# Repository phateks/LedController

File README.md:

# LED Controller (ESP32-C3-Mini)

<table>
	<tr>
		<td></td>
		<td></td>
	</tr>
</table>

## Power
- Input: 12 or 24 VDC on J1 connector

## Connections for Digital LED
- DO (DATA) 
- LED+ = VCC
- LED- = GND

## Connections for Classic LED
- LED+ = VCC
- Dim- = GND

## External Switch (Momentary)

- S1 - Dim down
- S2 - Dim up
- Com - Second connection on the switch (common for both)

## GPIO Config

- IO4: DATA LED
- IO5: PWM LED
- IO6: Dim Up
- IO7: Dim Down
- TXD0/RXD0: 
- EN: reset/enable
- BOOT: bootloader (IO09)

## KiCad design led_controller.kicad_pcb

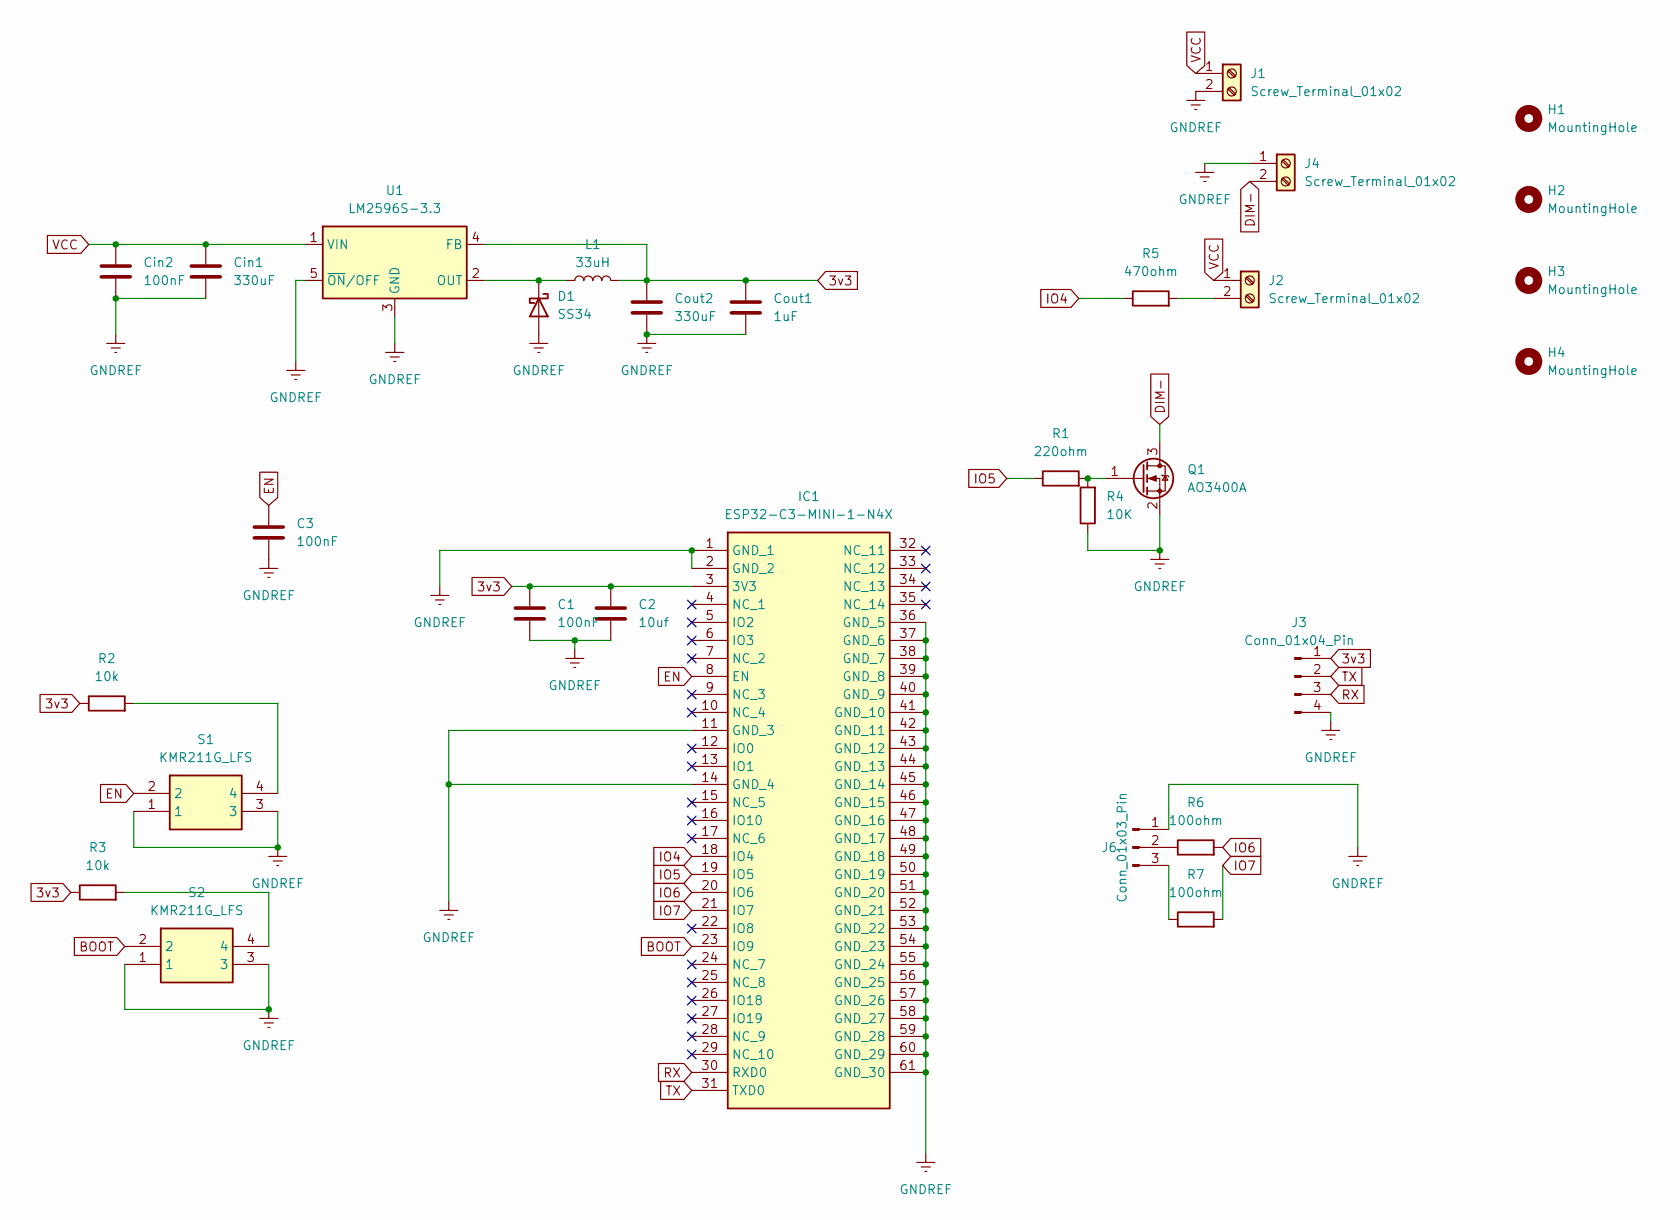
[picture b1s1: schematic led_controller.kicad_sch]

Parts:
C1, C3: 100nF
C2: 10uf; C_1206_3216Metric_Pad1.33x1.80mm_HandSolder
Cin1: 330uF; CP_Elec_8x10
Cin2: 100nF
Cout1: 1uF; C_1206_3216Metric_Pad1.33x1.80mm_HandSolder
Cout2: 330uF; CP_Elec_6.3x5.8
D1: SS34; D_SMA
H1, H2, H3, H4: MountingHole; MountingHole_3.2mm_M3
IC1: ESP32-C3-MINI-1-N4X; ESP32C3MINI1N4X; Manufacturer_Part_Number ESP32-C3-MINI-1-N4X
J1, J2, J4: Screw_Terminal_01x02; TerminalBlock_bornier-2_P5.08mm
J3: Conn_01x04_Pin; JST_EH_B4B-EH-A_1x04_P2.50mm_Vertical
J6: Conn_01x03_Pin; JST_EH_S3B-EH_1x03_P2.50mm_Horizontal
L1: 33uH; L_7.3x7.3_H4.5
Q1: AO3400A; SOT-23
R1: 220ohm
R2, R3: 10k
R4: 10K
R5: 470ohm
R6, R7: 100ohm
S1, S2: KMR211G_LFS; KMR_2; Manufacturer_Part_Number KMR211G LFS; Mouser Part Number 611-KMR211G-LFS
U1: LM2596S-3.3; TO-263-5_TabPin3

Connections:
3v3: C1.1, C2.1, Cout1.1, Cout2.1, IC1.3 (3V3), J3.1, L1.2, R2.1, R3.1, U1.4 (FB)
BOOT: IC1.23 (IO9), S2.2
DIM-: J4.2, Q1.3 (D)
EN: C3.1, IC1.8 (EN), S1.2
GNDREF: C1.2, C2.2, C3.2, Cin1.2, Cin2.2, Cout1.2, Cout2.2, D1.2 (A), IC1.1 (GND_1), IC1.2 (GND_2), IC1.11 (GND_3), IC1.14 (GND_4), IC1.36 (GND_5), IC1.37 (GND_6), IC1.38 (GND_7), IC1.39 (GND_8), IC1.40 (GND_9), IC1.41 (GND_10), IC1.42 (GND_11), IC1.43 (GND_12), IC1.44 (GND_13), IC1.45 (GND_14), IC1.46 (GND_15), IC1.47 (GND_16), IC1.48 (GND_17), IC1.49 (GND_18), IC1.50 (GND_19), IC1.51 (GND_20), IC1.52 (GND_21), IC1.53 (GND_22), IC1.54 (GND_23), IC1.55 (GND_24), IC1.56 (GND_25), IC1.57 (GND_26), IC1.58 (GND_27), IC1.59 (GND_28), IC1.60 (GND_29), IC1.61 (GND_30), J1.2, J3.4, J4.1, J6.1, Q1.2 (S), R4.1, S1.1, S1.3, S2.1, S2.3, U1.3 (GND), U1.5 (~ON/OFF)
IO4: IC1.18 (IO4), R5.1
IO5: IC1.19 (IO5), R1.1
IO6: IC1.20 (IO6), R6.2
IO7: IC1.21 (IO7), R7.2
unnamed: D1.1 (K), L1.1, U1.2 (OUT)
unnamed: J2.2, R5.2
unnamed: J6.2, R6.1
unnamed: J6.3, R7.1
unnamed: Q1.1 (G), R1.2, R4.2
unnamed: R2.2, S1.4
unnamed: R3.2, S2.4
RX: IC1.30 (RXD0), J3.3
TX: IC1.31 (TXD0), J3.2
VCC: Cin1.1, Cin2.1, J1.1, J2.1, U1.1 (VIN)

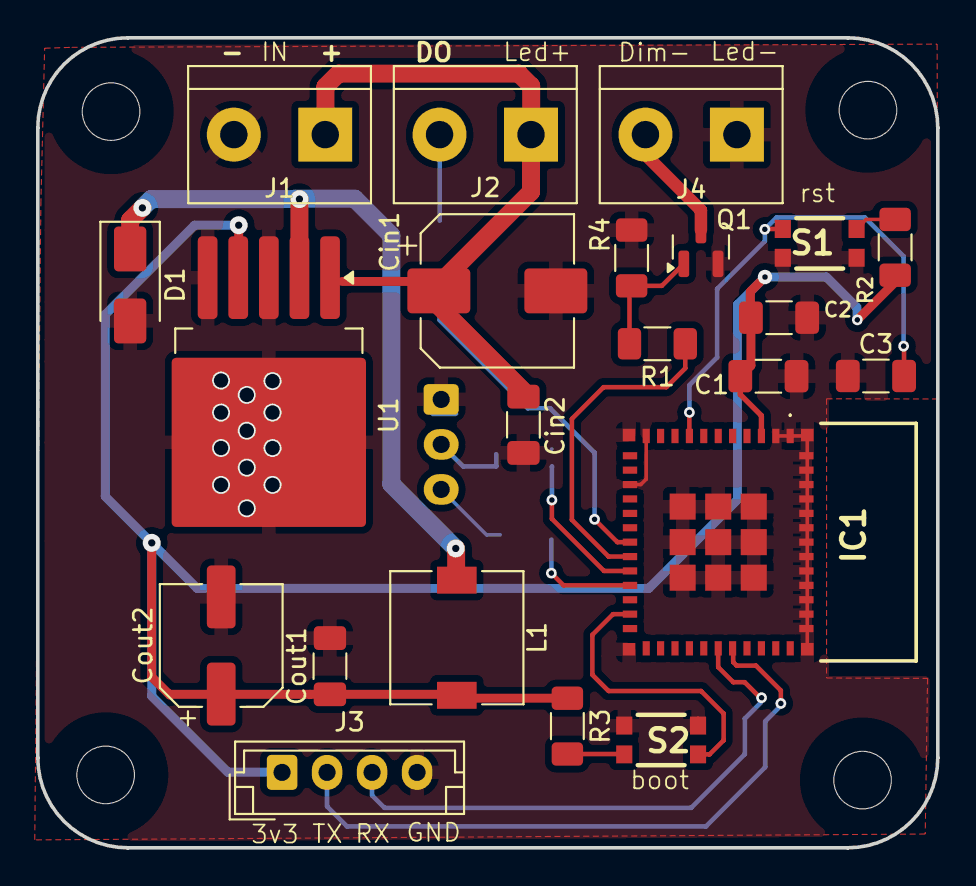
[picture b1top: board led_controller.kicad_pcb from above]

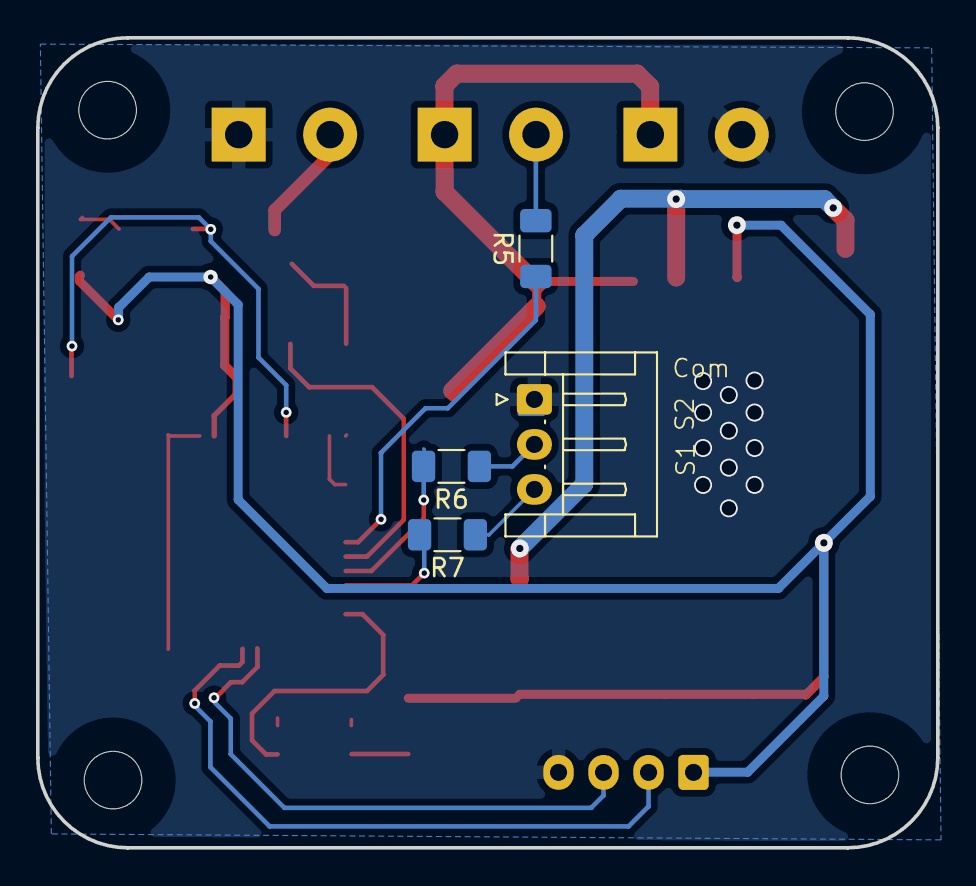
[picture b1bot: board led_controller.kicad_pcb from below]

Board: 2 copper layers, 50.0 x 45.0 mm, 30 parts (4 on the bottom side), 19 nets.

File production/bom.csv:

Designator,Footprint,Quantity,Value,LCSC Part #
"C1, C3, CIN2",1206,3,100nF,
C2,1206,1,10uf,
CIN1,CP_Elec_8x10,1,330uF,
COUT1,1206,1,1uF,
COUT2,CP_Elec_6.3x5.8,1,330uF,
D1,D_SMA,1,SS34,
IC1,ESP32C3MINI1N4X,1,ESP32-C3-MINI-1-N4X,
"J1, J2, J4",TerminalBlock_bornier-2_P5.08mm,3,Screw_Terminal_01x02,
J3,JST_EH_B4B-EH-A_1x04_P2.50mm_Vertical,1,Conn_01x04_Pin,
J6,JST_EH_S3B-EH_1x03_P2.50mm_Horizontal,1,Conn_01x03_Pin,
L1,L_7.3x7.3_H4.5,1,33uH,
Q1,SOT-23,1,AO3400A,
R1,1206,1,220ohm,
"R2, R3, R4",1206,3,10k,
R5,1206,1,470ohm,
"R6, R7",1206,2,100ohm,
"S1, S2",KMR_2,2,KMR211G_LFS,
U1,TO-263-5_TabPin3,1,LM2596S-3.3,

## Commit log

2026-03-20 Add initial README for LED Controller project
    Added detailed information about the LED controller, including power requirements, connections, external switch configuration, and GPIO settings.
2026-03-20 Fix image paths in README.md
    Updated image paths in README to use relative URLs.
2026-03-20 Update README to use HTML table for images
    Replaced image markdown with HTML table for better layout.
2026-03-20 Update README with PCB images
2026-03-20 Rename top_layer.png to top_layer_new.png
2026-03-20 Update PCB top image in README
2026-03-20 kicad10 and modified antenna
2026-03-20 production
